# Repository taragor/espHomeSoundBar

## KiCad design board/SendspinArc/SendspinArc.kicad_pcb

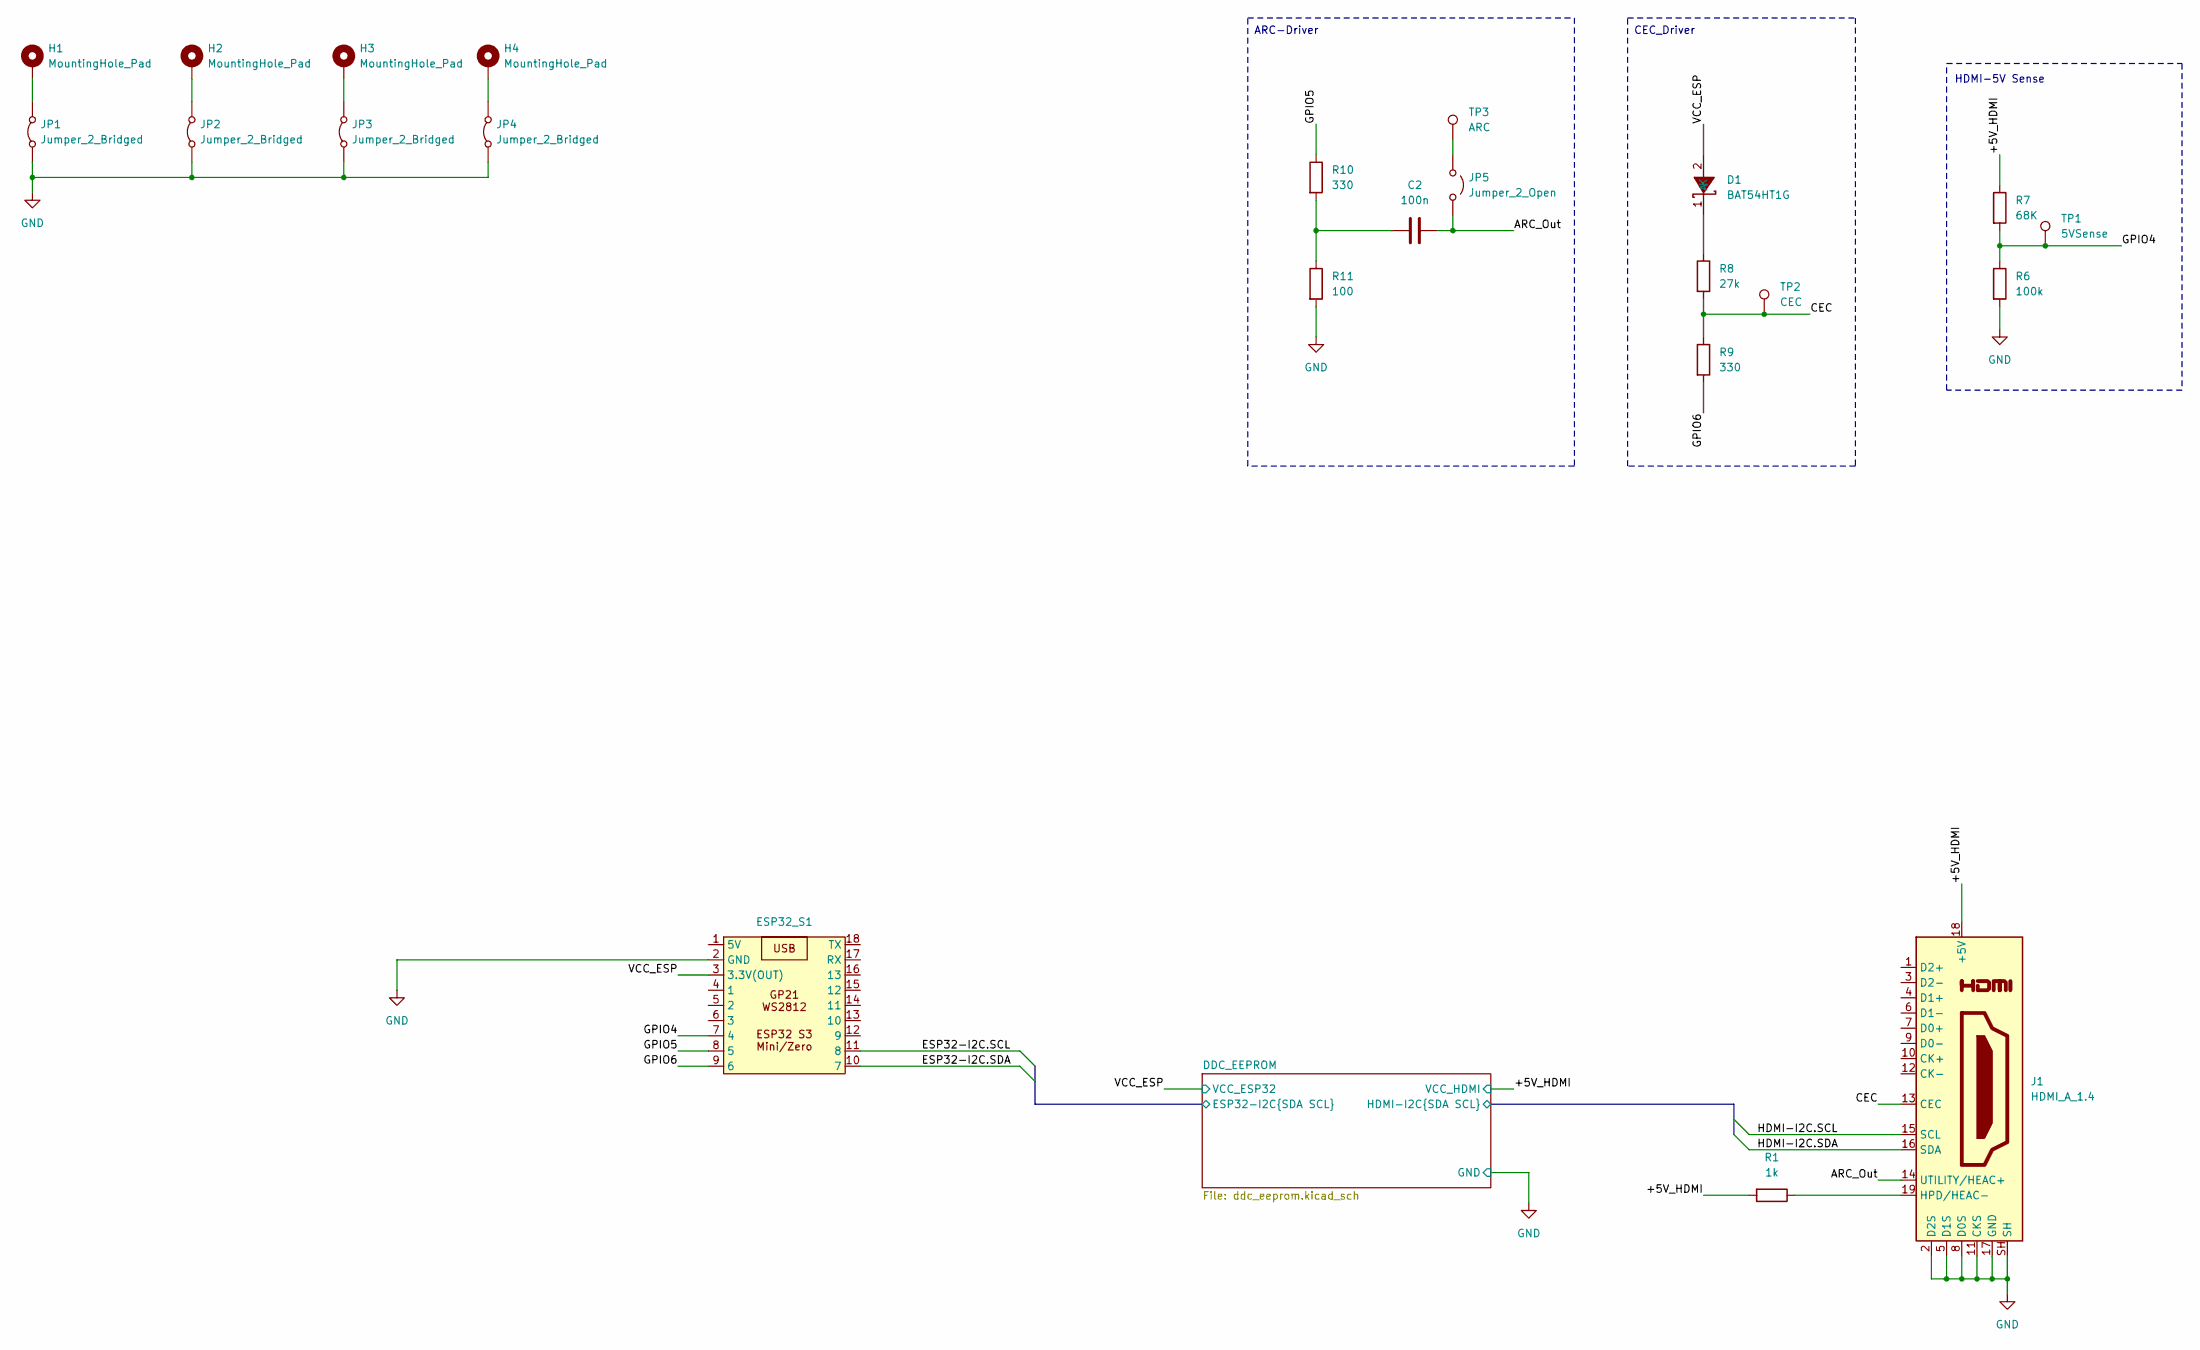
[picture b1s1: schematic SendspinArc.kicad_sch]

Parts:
C2: 100n; C_0603
D1: BAT54HT1G; D_SOD-323; Manufacturer Part BAT54HT1G; LCSC C21107
ESP32_S1: Waveshare_ESP32_S3_Zero_SMD
H1, H2, H3, H4: MountingHole_Pad; MountingHole_3.2mm_M3_DIN965_Pad_TopBottom
J1: HDMI_A_1.4; HDMI_A_Molex_208658-1001_Horizontal; LCSC C720616
JP1, JP2, JP3, JP4: Jumper_2_Bridged; SolderJumper-2_P1.3mm_Bridged_Pad1.0x1.5mm
JP5: Jumper_2_Open; SolderJumper-2_P1.3mm_Open_RoundedPad1.0x1.5mm
R1: 1k; R_0603_1608Metric
R6: 100k; R_0603_1608Metric
R7: 68K; R_0603_1608Metric
R8: 27k; R_0603_1608Metric
R9, R10: 330; R_0603_1608Metric
R11: 100; R_0603_1608Metric
TP1: 5VSense; PinHeader_1x01_P2.54mm_Vertical
TP2: CEC; PinHeader_1x01_P2.54mm_Vertical
TP3: ARC; PinHeader_1x01_P2.54mm_Vertical

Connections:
/+5V_HDMI: J1.18 (+5V), R1.2, R7.1; also elsewhere on the board
/ARC_Out: C2.2, J1.14 (UTILITY/HEAC+), JP5.2 (B)
/CEC: J1.13 (CEC), R8.2, R9.1, TP2.1 (1_1)
/DDC_EEPROM/ESP32-I2C.SCL: ESP32_S1.11 (8); also elsewhere on the board
/DDC_EEPROM/ESP32-I2C.SDA: ESP32_S1.10 (7); also elsewhere on the board
/DDC_EEPROM/HDMI-I2C.SCL: J1.15 (SCL); also elsewhere on the board
/DDC_EEPROM/HDMI-I2C.SDA: J1.16 (SDA); also elsewhere on the board
/GPIO4: ESP32_S1.7 (4), R6.1, R7.2, TP1.1 (1_1)
/GPIO5: ESP32_S1.8 (5), R10.1
/GPIO6: ESP32_S1.9 (6), R9.2
/VCC_ESP: D1.2 (A), ESP32_S1.3 (3.3V(OUT)); also elsewhere on the board
GND: ESP32_S1.2 (GND), J1.2 (D2S), J1.5 (D1S), J1.8 (D0S), J1.11 (CKS), J1.17 (GND), J1.SH, JP1.1 (A), JP2.1 (A), JP3.1 (A), JP4.1 (A), R6.2, R11.2; also elsewhere on the board
unnamed: C2.1, R10.2, R11.1
unnamed: D1.1 (K), R8.1
unnamed: J1.19 (HPD/HEAC-), R1.1
unnamed: H1.1 (1_1), JP1.2 (B)
unnamed: H2.1 (1_1), JP2.2 (B)
unnamed: H3.1 (1_1), JP3.2 (B)
unnamed: H4.1 (1_1), JP4.2 (B)
unnamed: JP5.1 (A), TP3.1 (1_1)

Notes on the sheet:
ARC-Driver
CEC_Driver
HDMI-5V Sense

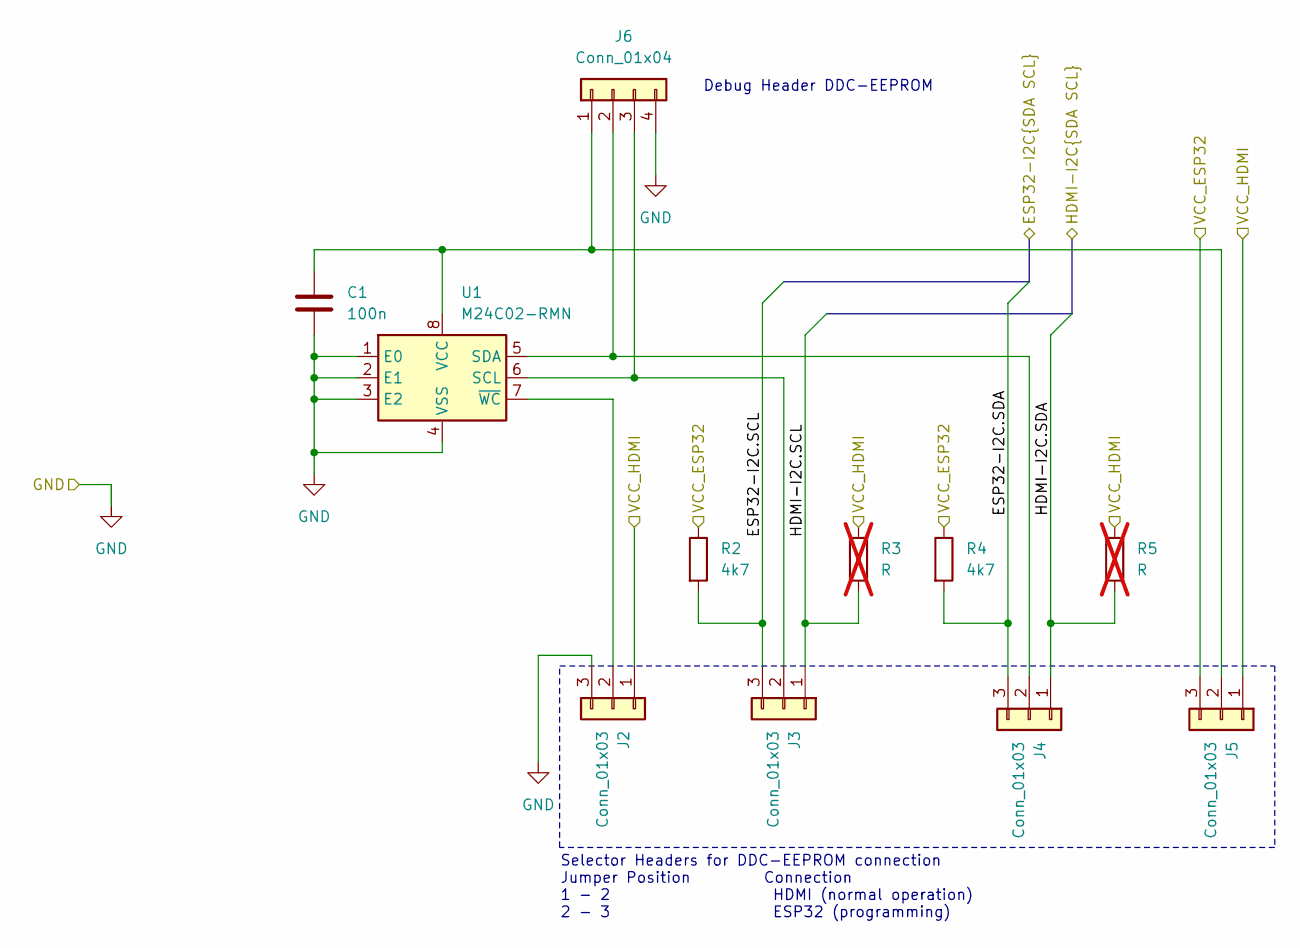
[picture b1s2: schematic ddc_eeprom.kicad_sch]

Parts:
C1: 100n; C_0603
J2, J3, J4, J5: Conn_01x03; PinHeader_1x03_P2.54mm_Vertical
J6: Conn_01x04; PinHeader_1x04_P2.54mm_Vertical; LCSC C160334
R2, R4: 4k7; R_0603_1608Metric
R3, R5: R; R_0603_1608Metric; not fitted
U1: M24C02-RMN; SOIC-8_3.9x4.9mm_P1.27mm; LCSC C83836

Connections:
/+5V_HDMI: J2.1, J5.1, R3.1, R5.1; also elsewhere on the board
/DDC_EEPROM/ESP32-I2C.SCL: J3.3, R2.2; also elsewhere on the board
/DDC_EEPROM/ESP32-I2C.SDA: J4.3, R4.2; also elsewhere on the board
/DDC_EEPROM/HDMI-I2C.SCL: J3.1, R3.2; also elsewhere on the board
/DDC_EEPROM/HDMI-I2C.SDA: J4.1, R5.2; also elsewhere on the board
/VCC_ESP: J5.3, R2.1, R4.1; also elsewhere on the board
GND: C1.1, J2.3, J6.4, U1.1 (E0), U1.2 (E1), U1.3 (E2), U1.4 (VSS); also elsewhere on the board
unnamed: J2.2, U1.7 (~WC)
unnamed: J3.2, J6.3, U1.6 (SCL)
unnamed: J4.2, J6.2, U1.5 (SDA)
unnamed: C1.2, J5.2, J6.1, U1.8 (VCC)

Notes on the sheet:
Selector Headers for DDC-EEPROM connection Jumper Position Connection 1 - 2 HDMI (normal operation) 2 - 3 ESP32 (programming)
Debug Header DDC-EEPROM

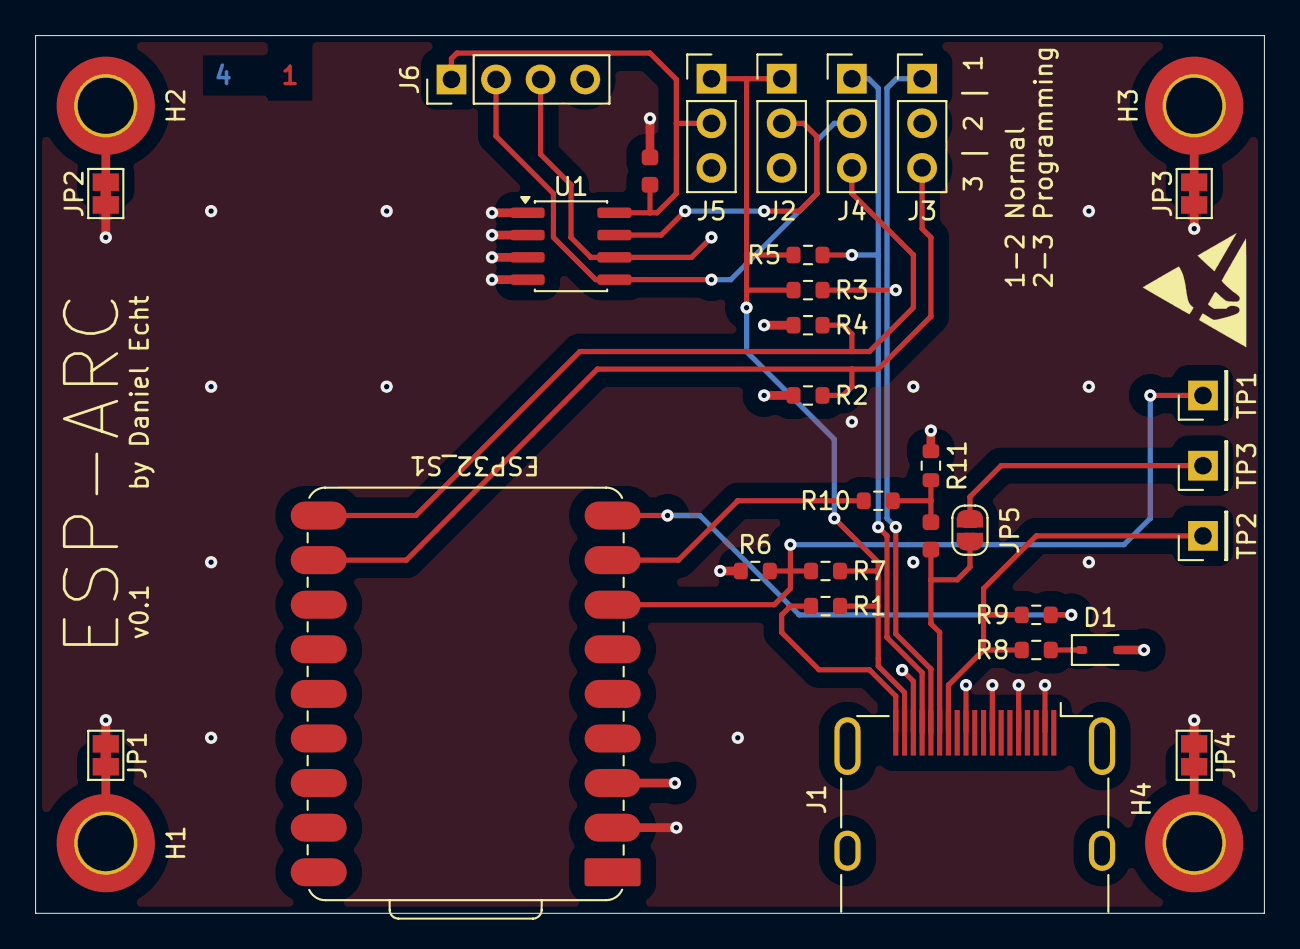
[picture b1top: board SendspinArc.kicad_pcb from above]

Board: 4 copper layers, 70.0 x 50.0 mm, 35 parts (0 on the bottom side), 24 nets.

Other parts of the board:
ESD-Mark: ESD-Logo_6.6x6mm_SilkScreen

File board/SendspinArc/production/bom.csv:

Designator,Footprint,Quantity,Value,LCSC Part #
"C1, C2",C_0603,2,100n,
D1,D_SOD-323,1,BAT54HT1G,C21107
ESP32_S1,Waveshare_ESP32_S3_Zero_SMD,1,~,
J1,HDMI_A_Molex_208658-1001_Horizontal,1,HDMI_A_1.4,C720616
"J2, J3, J4, J5",PinHeader_1x03_P2.54mm_Vertical,4,Conn_01x03,
J6,PinHeader_1x04_P2.54mm_Vertical,1,Conn_01x04,C160334
"JP1, JP2, JP3, JP4",SolderJumper-2_P1.3mm_Bridged_Pad1.0x1.5mm,4,Jumper_2_Bridged,
JP5,SolderJumper-2_P1.3mm_Open_RoundedPad1.0x1.5mm,1,Jumper_2_Open,
R1,0603,1,1k,
"R10, R9",0603,2,330,
R11,0603,1,100,
"R2, R4",0603,2,4k7,
R6,0603,1,100k,
R7,0603,1,68K,
R8,0603,1,27k,
TP1,PinHeader_1x01_P2.54mm_Vertical,1,5VSense,
TP2,PinHeader_1x01_P2.54mm_Vertical,1,CEC,
TP3,PinHeader_1x01_P2.54mm_Vertical,1,ARC,
U1,SOIC-8_3.9x4.9mm_P1.27mm,1,M24C02-RMN,C83836
